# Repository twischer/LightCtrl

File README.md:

# LightCtrl
Use ESP8266 to control string lights, RGB LEDs or light bulbs over MQTT and ArtNet

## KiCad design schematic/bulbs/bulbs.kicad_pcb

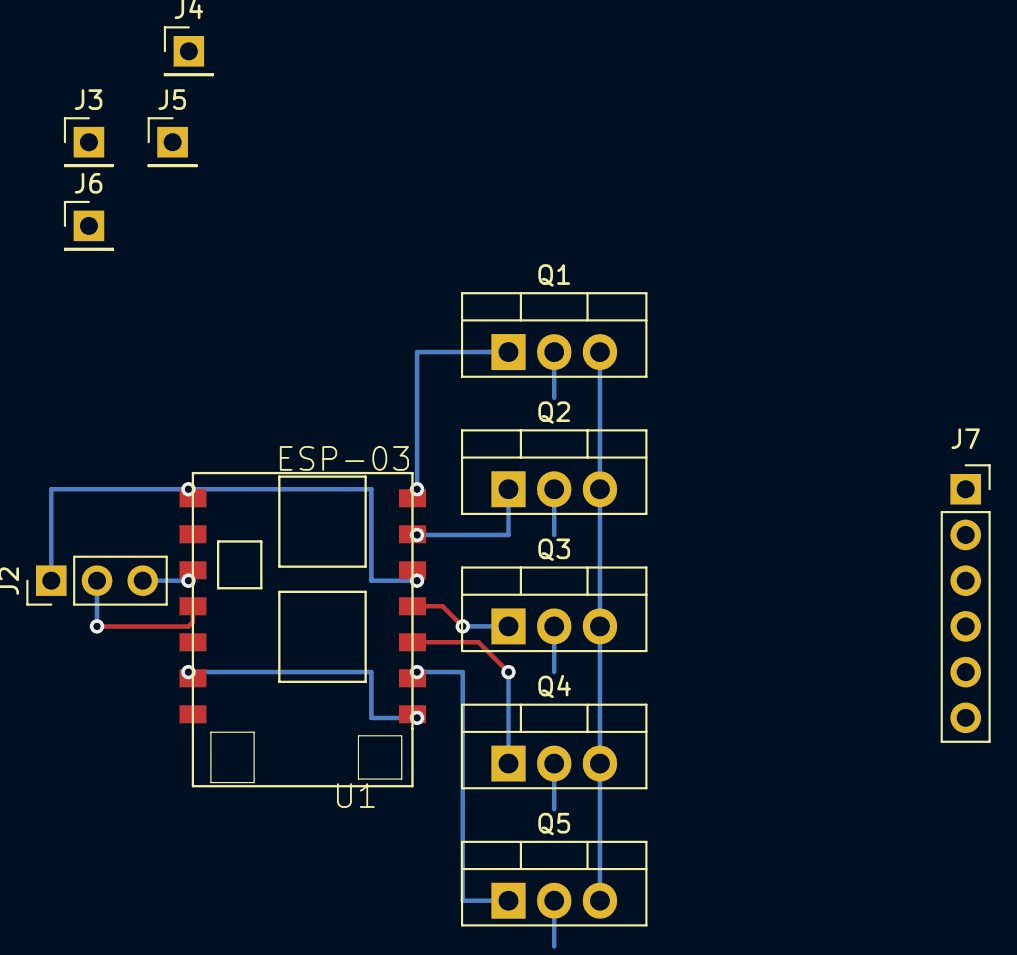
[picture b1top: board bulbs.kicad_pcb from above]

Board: 2 copper layers, 12 parts (0 on the bottom side), 15 nets.

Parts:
J2: Download; PinHeader_1x03_P2.54mm_Vertical
J3, J4: GND; PinHeader_1x01_P2.54mm_Vertical
J5: 230V; PinHeader_1x01_P2.54mm_Vertical
J6: 2V6; PinHeader_1x01_P2.54mm_Vertical
J7: Bulbs; PinSocket_1x06_P2.54mm_Vertical
Q1, Q2, Q3, Q4, Q5: IPP60R750; TO-220-3_Vertical
U1: ESP-03

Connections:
GND: J2.1, J3.1, J4.1, Q1.3, Q2.3, Q3.3, Q4.3, Q5.3, U1.1, U1.12
unnamed: J5.1, J7.1
unnamed: J2.2, U1.4
unnamed: J2.3, U1.3
unnamed: J6.1, U1.6, U1.8
unnamed: J7.2, Q1.2
unnamed: J7.3, Q2.2
unnamed: J7.4, Q3.2
unnamed: J7.5, Q4.2
unnamed: J7.6, Q5.2
unnamed: Q1.1, U1.14
unnamed: Q2.1, U1.13
unnamed: Q3.1, U1.11
unnamed: Q4.1, U1.10
unnamed: Q5.1, U1.9

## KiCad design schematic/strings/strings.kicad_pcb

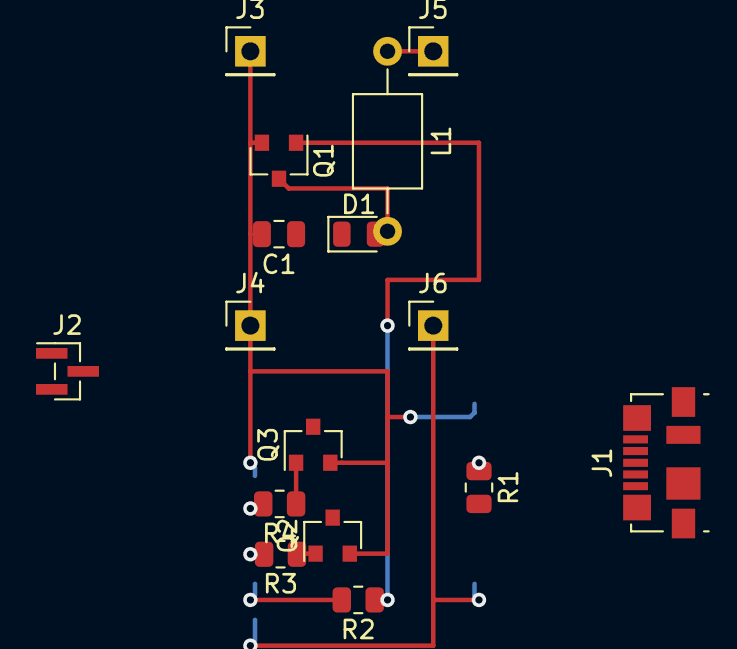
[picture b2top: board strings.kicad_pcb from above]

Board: 2 copper layers, 17 parts (1 on the bottom side), 16 nets.

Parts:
C1: 1µ; C_0805_2012Metric
D1: D; D_0805_2012Metric
J1: USB_B_Micro; USB_Micro-B_Molex_47346-0001
J2: StringLights; PinHeader_1x03_P1.00mm_Vertical_SMD_Pin1Left
J3, J4: GND; PinHeader_1x01_P2.54mm_Vertical
J5: 5V; PinHeader_1x01_P2.54mm_Vertical
J6: 2V6; PinHeader_1x01_P2.54mm_Vertical
L1: 220µ; L_Axial_L5.0mm_D3.6mm_P10.00mm_Horizontal_Murata_BL01RN1A2A2
Q1, Q2, Q3: MMBT5551L; SOT-23
R1: 0?R; R_0805_2012Metric
R2: 1k5; R_0805_2012Metric
R3, R4: 6k8; R_0805_2012Metric
U1: ESP-03

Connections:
/32V: C1.1, D1.1, J2.1
GND: C1.2, J1.5, J1.6, J3.1, J4.1, Q1.2, Q2.2, Q3.2, U1.1, U1.12
unnamed: D1.2, L1.2, Q1.3
unnamed: J1.1, J5.1, L1.1
unnamed: J1.2, R1.2
unnamed: J1.3, U1.4
unnamed: J2.2, Q2.3
unnamed: J2.3, Q3.3
unnamed: J6.1, U1.6, U1.8
unnamed: Q1.1, R2.1
unnamed: Q2.1, R3.1
unnamed: Q3.1, R4.1
unnamed: R1.1, U1.3
unnamed: R2.2, U1.9
unnamed: R3.2, U1.10
unnamed: R4.2, U1.11

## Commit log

2021-02-05 Reboot afterwards fails with exception
2021-02-05 Use reboot UART mode of EspClass
2021-02-05 reboot_bootloader: Working after soft_reset
    Tested with
    $ /usr/bin/python3 \
    /home/timo/.platformio/packages/tool-esptoolpy/esptool.py \
    --no-stub --before no_reset --after soft_reset --chip esp8266 \
    --port /dev/ttyUSB0 --baud 460800 write_flash 0x0 \
    .pio/build/d1_mini/firmware.bin
2021-02-05 Working reboot without stub
2021-02-05 schematic: Add for 2ch string lights
2021-02-05 schematic: Add for 5ch 230V light bulbs
